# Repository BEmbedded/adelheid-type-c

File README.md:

# Work In Progress
Copied in the USB-C port from the ArisuTea port.

# 𝕬𝖉𝖊𝖑𝖍𝖊𝖎𝖉

The Adelheid is a 75% Alice-like keyboard.  
It's a fork of FateNozomi's Arisu files: [Arisu PCB](https://github.com/FateNozomi/arisu-pcb) &amp; [Arisu case](https://github.com/FateNozomi/arisu-case)

<!--  -->

This repository includes files for:

- the Adelheid PCB &rarr; [README.md](./pcb/README.md)
- a layered case &rarr; [README.md](./case/README.md)
- a wrist rest &rarr; [README.md](./wrist-rest/README.md)

## Changes in this fork

Here is a list of things I added in this fork in comparison to the Arisu:

- [x] added an angled &amp; spaced function row
- [x] added option for stepped caps lock
- [x] replaced micro usb port with tht mini usb port
- [x] added single color underglow and key lighting

for a visual comparison see [here](./IMAGES.md#arisu-comparison)

## Layout

A spaced 75% layout on top of the Alice/Arisu-layout.

[Keyboard-Layout-Editor](http://www.keyboard-layout-editor.com/#/gists/4262535adb5ac81a913edbebc4de8226) [(raw)](https://gist.github.com/floookay/4262535adb5ac81a913edbebc4de8226)  
  
<!--  -->

## Firmware

In the QMK repository: <https://github.com/qmk/qmk_firmware/tree/master/keyboards/adelheid>  
And the online configurator: https://config.qmk.fm/#/adelheid/LAYOUT

## Images

For more images see [images.md](./IMAGES.md).

## Miscellaneous

> Why?

I think accessing the function keys with a layer on the number row is the superior method as it's faster and more comfortable because you barely have to move your hands. I found myself trying to access the function row one-handedly quite often and nothing beats the comfort of pressing a single dedicated key. By default you can still access the function keys via the number row on the secondary layer.

> Where does the name Adelheid come from?

I thought it'd be nice to continue the somewhat tradition of naming Alice-clones by putting a spin on the forename Alice, just like the Arisu, Lisa and Majbritt did. I chose Adelheid as a German spin on the name.  
The typeface is called Fraktur and was the dominant typeface during the time when Adelheid was one of the most popular names.

> Will you add more keys to the bottom row or a second B key?

I don't plan on changing the bottom row or adding a second B key. In my opinion the keyboard looks the best and most balanced the way Fate designed it.

## TODO's

- add 3d printable case files

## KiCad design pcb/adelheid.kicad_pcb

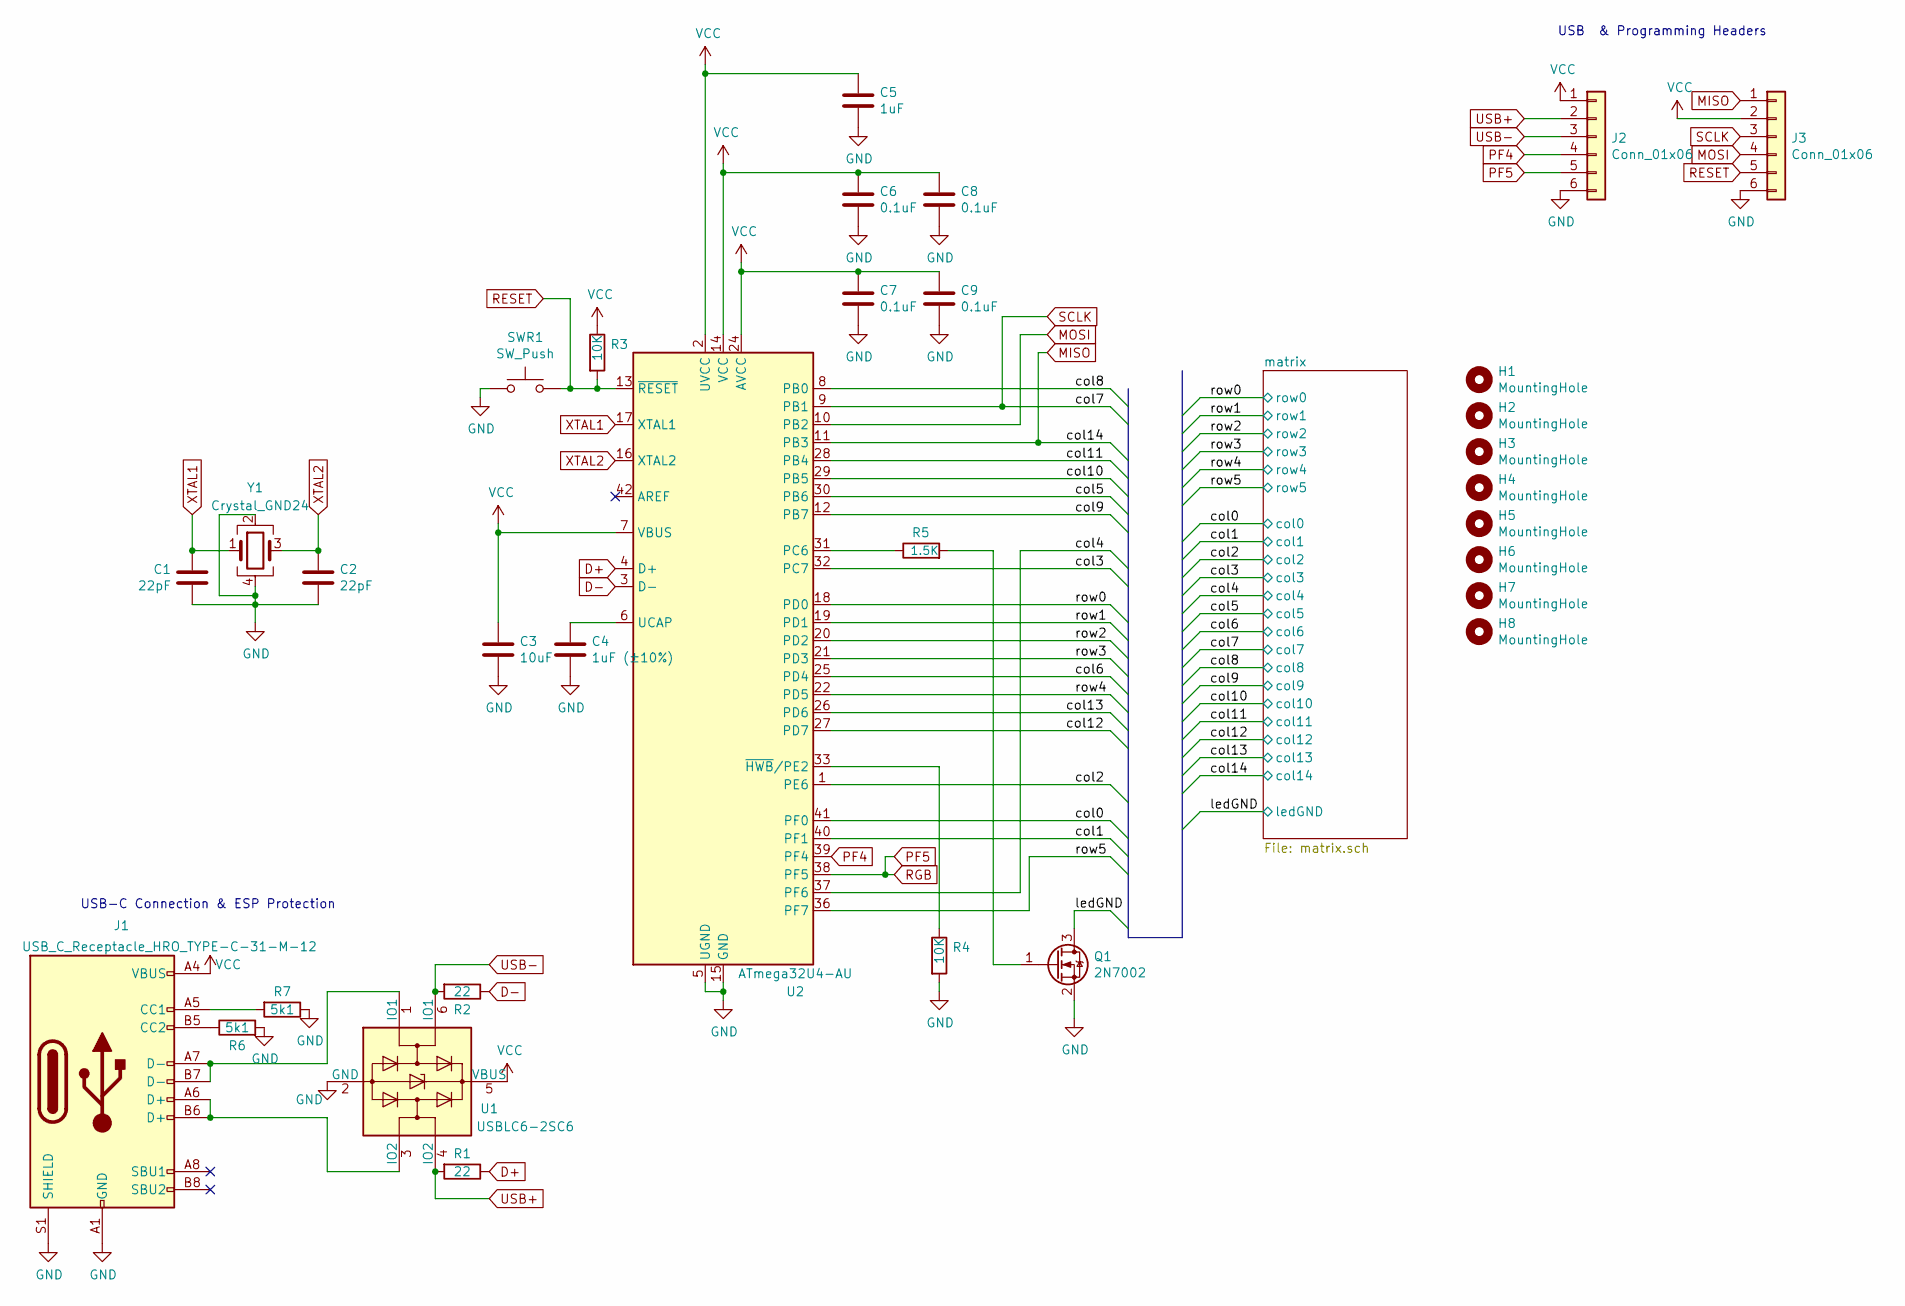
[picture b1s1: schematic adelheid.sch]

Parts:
C1, C2: 22pF; C_0805_HandSoldering; LCSC C1804
C3: 10uF; C_0805_HandSoldering; LCSC C15850
C4: 1uF (±10%); C_0805_HandSoldering; LCSC C28323
C5: 1uF; C_0805_HandSoldering; LCSC C28323
C6, C7, C8, C9: 0.1uF; C_0805_HandSoldering; LCSC C49678
H1, H2, H3, H4, H5, H6, H7, H8: MountingHole; MountingHole_2.2mm_M2_Pad
J1: USB_C_Receptacle_HRO_TYPE-C-31-M-12; USB_C_Receptacle_HRO_TYPE-C-31-M-12-HandSoldering; LCSC C319148
J2, J3: Conn_01x06; PinHeader_1x06_P2.54mm_Vertical
Q1: 2N7002; SOT-23; LCSC C8545
R1, R2: 22; R_0805_2012Metric_Pad1.15x1.40mm_HandSolder; LCSC C17561
R3, R4: 10K; R_0805_2012Metric_Pad1.15x1.40mm_HandSolder; LCSC C17414
R5: 1.5K; R_0805_2012Metric_Pad1.15x1.40mm_HandSolder; LCSC C4310
R6, R7: 5k1; R_0805_2012Metric_Pad1.20x1.40mm_HandSolder; LCSC C27834
SWR1: SW_Push; SW_SPST_TL3342; LCSC C318884
U1: USBLC6-2SC6; SOT-23-6_Handsoldering; LCSC C7519
U2: ATmega32U4-AU; TQFP-44_10x10mm_Pitch0.8mm; LCSC C44854
Y1: Crystal_GND24; Crystal_SMD_SeikoEpson_FA238-4pin_3.2x2.5mm_HandSoldering; LCSC C13738

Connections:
/col0: U2.41 (PF0); also elsewhere on the board
/col1: U2.40 (PF1); also elsewhere on the board
/col2: U2.1 (PE6); also elsewhere on the board
/col3: U2.32 (PC7); also elsewhere on the board
/col4: U2.37 (PF6); also elsewhere on the board
/col5: U2.30 (PB6); also elsewhere on the board
/col6: U2.25 (PD4); also elsewhere on the board
/col8: U2.8 (PB0); also elsewhere on the board
/col9: U2.12 (PB7); also elsewhere on the board
/col10: U2.29 (PB5); also elsewhere on the board
/col11: U2.28 (PB4); also elsewhere on the board
/col12: U2.27 (PD7); also elsewhere on the board
/col13: U2.26 (PD6); also elsewhere on the board
/ledGND: Q1.3 (D); also elsewhere on the board
/row0: U2.18 (PD0); also elsewhere on the board
/row1: U2.19 (PD1); also elsewhere on the board
/row2: U2.20 (PD2); also elsewhere on the board
/row3: U2.21 (PD3); also elsewhere on the board
/row4: U2.22 (PD5); also elsewhere on the board
/row5: U2.36 (PF7); also elsewhere on the board
D+: R1.1, U2.4 (D+)
D-: R2.1, U2.3 (D-)
GND: C1.1, C2.2, C3.2, C4.2, C5.2, C6.2, C7.2, C8.2, C9.2, J1.A1 (GND), J1.A12 (GND), J1.S1 (SHIELD), J2.6, J3.6, Q1.2 (S), R4.2, R6.2, R7.1, SWR1.1, U1.2 (GND), U2.5 (UGND), U2.15 (GND), U2.23 (GND), U2.35 (GND), U2.43 (GND), Y1.2, Y1.4; also elsewhere on the board
MISO: J3.1, U2.11 (PB3); also elsewhere on the board
MOSI: J3.4, U2.10 (PB2)
unnamed: C4.1, U2.6 (UCAP)
unnamed: J1.A5 (CC1), R7.2
unnamed: J1.A6 (D+), J1.B6 (D+), U1.3 (IO2)
unnamed: J1.A7 (D-), J1.B7 (D-), U1.1 (IO1)
unnamed: J1.B5 (CC2), R6.1
unnamed: Q1.1 (G), R5.2
unnamed: R4.1, U2.33 (~HWB~/PE2)
unnamed: R5.1, U2.31 (PC6)
PF4: J2.4, U2.39 (PF4)
PF5: J2.5, U2.38 (PF5); also elsewhere on the board
RESET: J3.5, R3.2, SWR1.2, U2.13 (~RESET)
SCLK: J3.3, U2.9 (PB1); also elsewhere on the board
USB+: J2.2, R1.2, U1.4 (IO2)
USB-: J2.3, R2.2, U1.6 (IO1)
VCC: C3.1, C5.1, C6.1, C7.1, C8.1, C9.1, J1.A4 (VBUS), J1.A9 (VBUS), J2.1, J3.2, R3.1, U1.5 (VBUS), U2.2 (UVCC), U2.7 (VBUS), U2.14 (VCC), U2.24 (AVCC), U2.34 (VCC), U2.44 (AVCC); also elsewhere on the board
XTAL1: C1.2, U2.17 (XTAL1), Y1.1
XTAL2: C2.1, U2.16 (XTAL2), Y1.3

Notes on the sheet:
USB & Programming Headers
USB-C Connection & ESP Protection

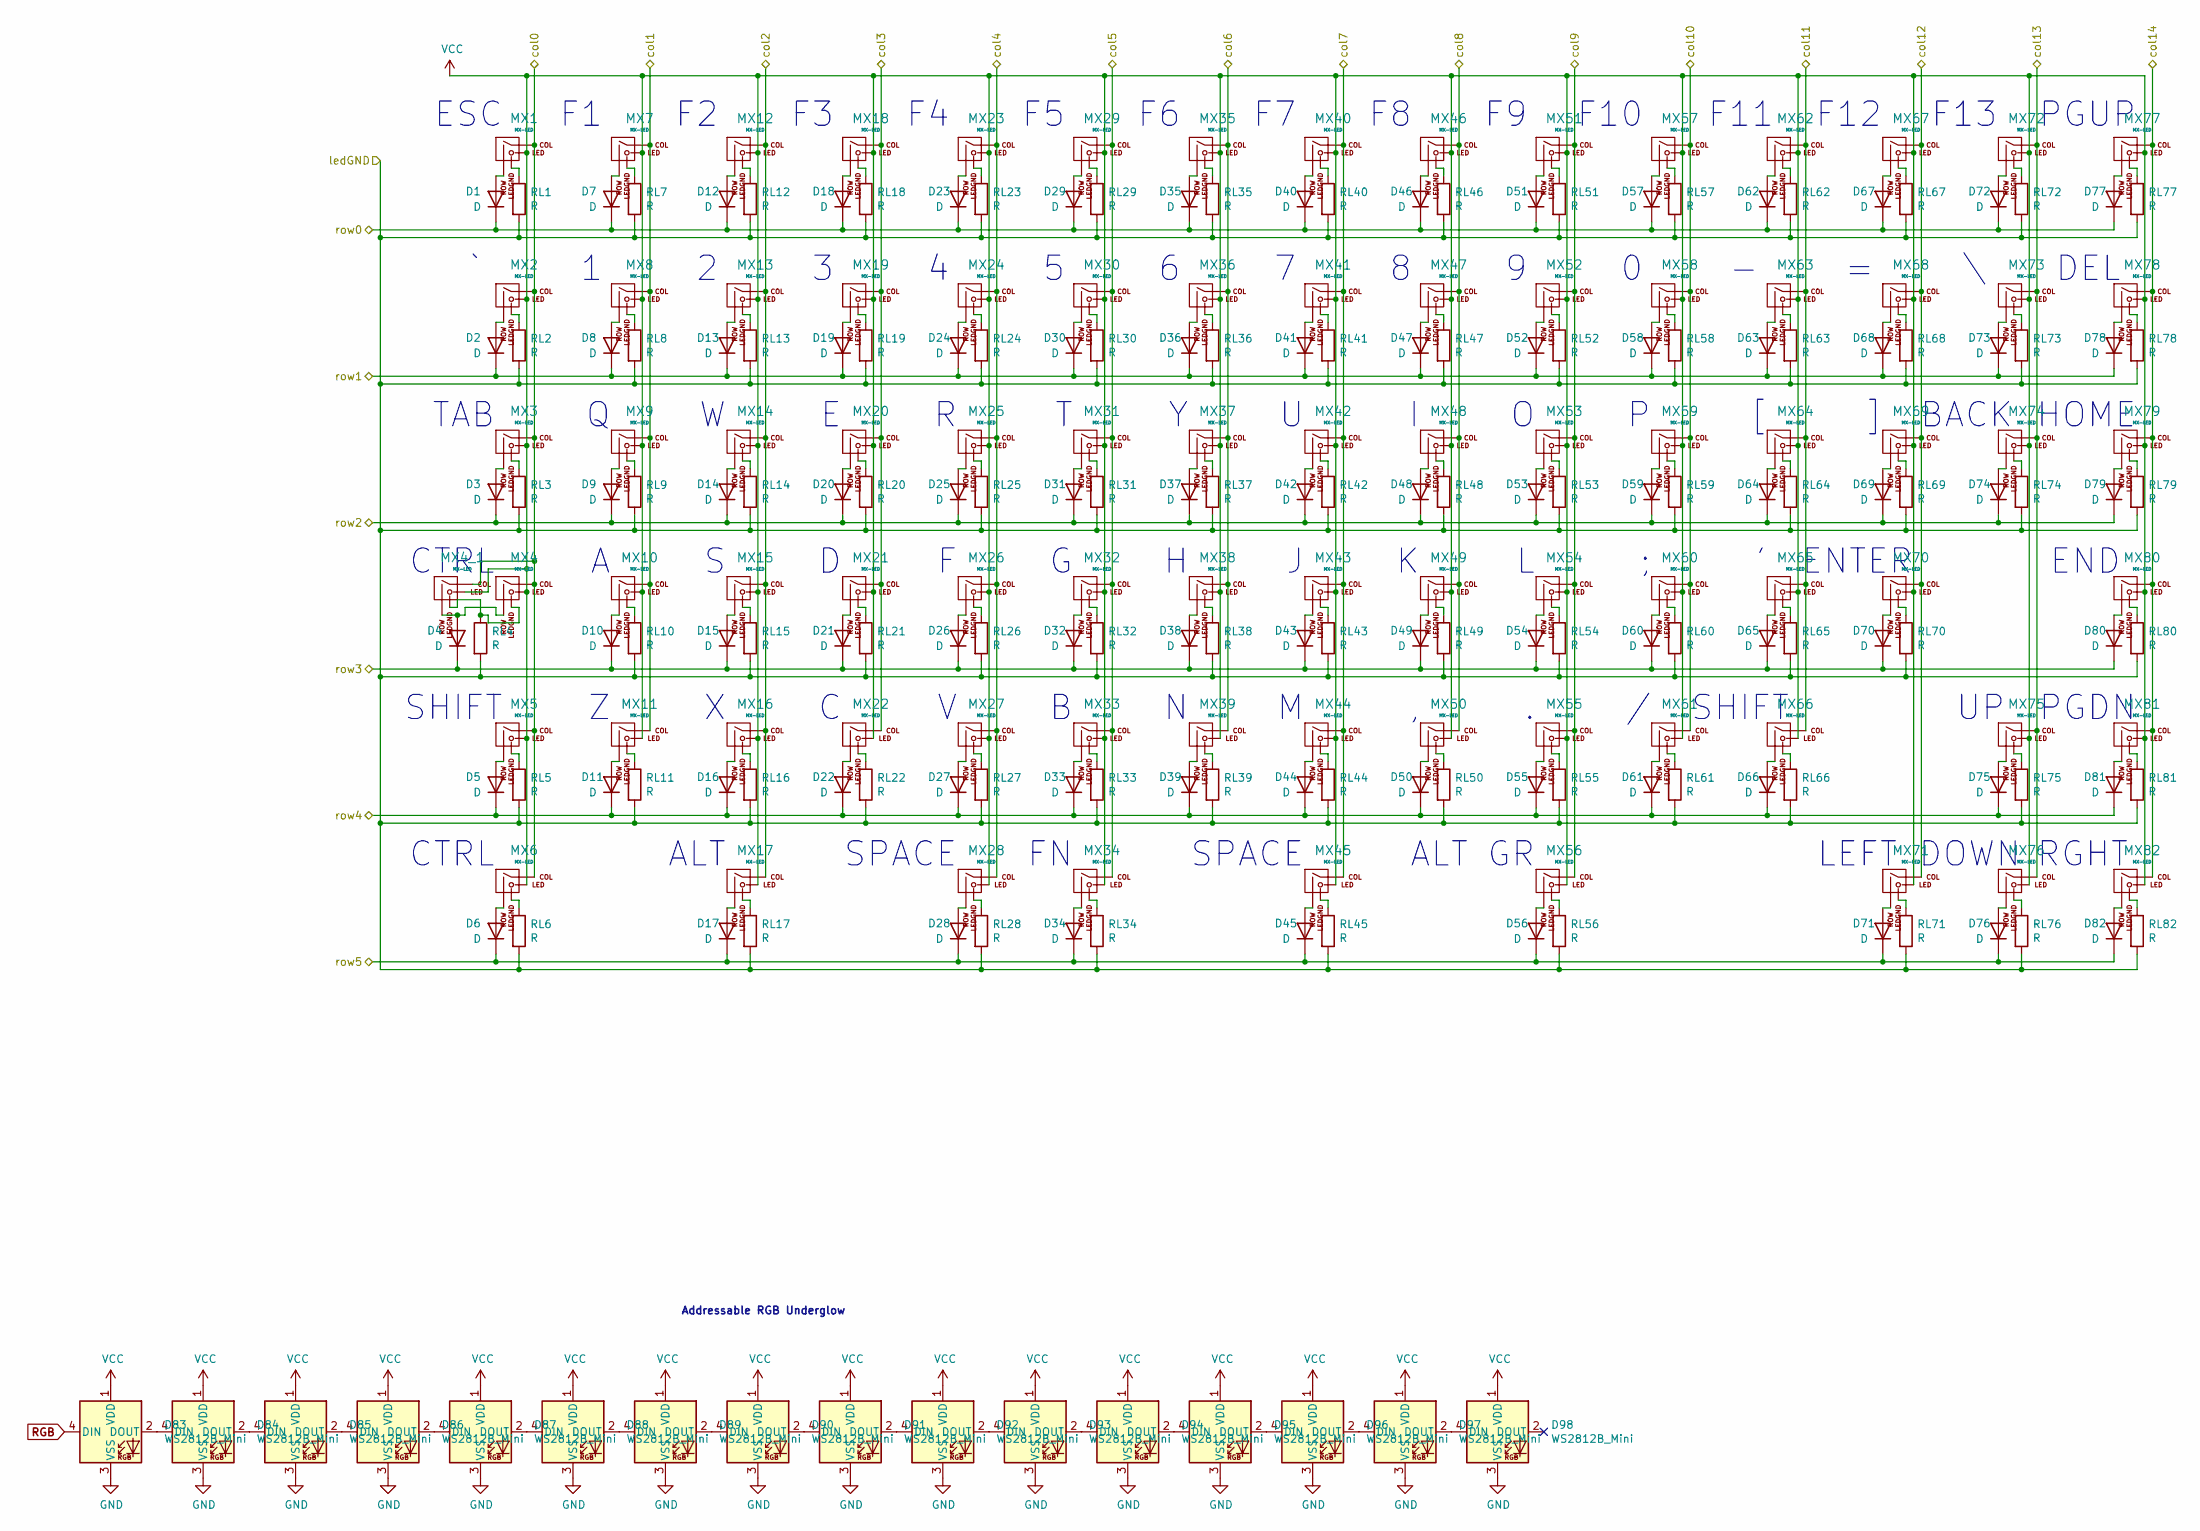
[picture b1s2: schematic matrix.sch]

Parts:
D1, D2, D3, D4, D5, D6, D7, D8, D9, D10, D11, D12, D13, D14, D15, D16, D17, D18, D19, D20, D21, D22, D23, D24, D25, D26, D27, D28, D29, D30, D31, D32, D33, D34, D35, D36, D37, D38, D39, D40, D41, D42, D43, D44, D45, D46, D47, D48, D49, D50, D51, D52, D53, D54, D55, D56, D57, D58, D59, D60, D61, D62, D63, D64, D65, D66, D67, D68, D69, D70, D71, D72, D73, D74, D75, D76, D77, D78, D79, D80, D81, D82: D; D_SOD-123; LCSC C241939
D83, D84, D85, D86, D87, D88, D89, D90, D91, D92, D93, D94, D95, D96, D97, D98: WS2812B_Mini; LED_SK6812MINI_PLCC4_3.5x3.5mm_P1.75mm; LCSC C114583
MX1, MX2, MX7, MX8, MX9, MX10, MX11, MX12, MX13, MX14, MX15, MX16, MX18, MX19, MX20, MX21, MX22, MX23, MX24, MX25, MX26, MX27, MX29, MX30, MX31, MX32, MX33, MX34, MX35, MX36, MX37, MX38, MX39, MX40, MX41, MX42, MX43, MX44, MX46, MX47, MX48, MX49, MX50, MX51, MX52, MX53, MX54, MX55, MX57, MX58, MX59, MX60, MX61, MX62, MX63, MX64, MX65, MX67, MX68, MX69, MX71, MX72, MX73, MX75, MX76, MX77, MX78, MX79, MX80, MX81, MX82: MX-LED; MXOnly-1U
MX3, MX6, MX17, MX56, MX74: MX-LED; MXOnly-1.5U
MX4, MX66: MX-LED; MXOnly-1.75U
MX4_1: MX-LED; MXOnly-1.75U-FLIPPED
MX5: MX-LED; MXOnly-2.25U
MX28: MX-LED; MXOnly-2U-ReversedStabilizers
MX45: MX-LED; MXOnly-2.75U-ReversedStabilizers
MX70: MX-LED; MXOnly-2.25U-ReversedStabilizers
RL1, RL2, RL3, RL4, RL5, RL6, RL7, RL8, RL9, RL10, RL11, RL12, RL13, RL14, RL15, RL16, RL17, RL18, RL19, RL20, RL21, RL22, RL23, RL24, RL25, RL26, RL27, RL28, RL29, RL30, RL31, RL32, RL33, RL34, RL35, RL36, RL37, RL38, RL39, RL40, RL41, RL42, RL43, RL44, RL45, RL46, RL47, RL48, RL49, RL50, RL51, RL52, RL53, RL54, RL55, RL56, RL57, RL58, RL59, RL60, RL61, RL62, RL63, RL64, RL65, RL66, RL67, RL68, RL69, RL70, RL71, RL72, RL73, RL74, RL75, RL76, RL77, RL78, RL79, RL80, RL81, RL82: R; R_0805_2012Metric_Pad1.15x1.40mm_HandSolder; LCSC C17798-DNP

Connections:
/col0: MX1.1 (COL), MX2.1 (COL), MX3.1 (COL), MX4.1 (COL), MX4_1.1 (COL), MX5.1 (COL), MX6.1 (COL); also elsewhere on the board
/col1: MX7.1 (COL), MX8.1 (COL), MX9.1 (COL), MX10.1 (COL), MX11.1 (COL); also elsewhere on the board
/col2: MX12.1 (COL), MX13.1 (COL), MX14.1 (COL), MX15.1 (COL), MX16.1 (COL), MX17.1 (COL); also elsewhere on the board
/col3: MX18.1 (COL), MX19.1 (COL), MX20.1 (COL), MX21.1 (COL), MX22.1 (COL); also elsewhere on the board
/col4: MX23.1 (COL), MX24.1 (COL), MX25.1 (COL), MX26.1 (COL), MX27.1 (COL), MX28.1 (COL); also elsewhere on the board
/col5: MX29.1 (COL), MX30.1 (COL), MX31.1 (COL), MX32.1 (COL), MX33.1 (COL), MX34.1 (COL); also elsewhere on the board
/col6: MX35.1 (COL), MX36.1 (COL), MX37.1 (COL), MX38.1 (COL), MX39.1 (COL); also elsewhere on the board
/col8: MX46.1 (COL), MX47.1 (COL), MX48.1 (COL), MX49.1 (COL), MX50.1 (COL); also elsewhere on the board
/col9: MX51.1 (COL), MX52.1 (COL), MX53.1 (COL), MX54.1 (COL), MX55.1 (COL), MX56.1 (COL); also elsewhere on the board
/col10: MX57.1 (COL), MX58.1 (COL), MX59.1 (COL), MX60.1 (COL), MX61.1 (COL); also elsewhere on the board
/col11: MX62.1 (COL), MX63.1 (COL), MX64.1 (COL), MX65.1 (COL), MX66.1 (COL); also elsewhere on the board
/col12: MX67.1 (COL), MX68.1 (COL), MX69.1 (COL), MX70.1 (COL), MX71.1 (COL); also elsewhere on the board
/col13: MX72.1 (COL), MX73.1 (COL), MX74.1 (COL), MX75.1 (COL), MX76.1 (COL); also elsewhere on the board
/ledGND: RL1.2, RL2.2, RL3.2, RL4.2, RL5.2, RL6.2, RL7.2, RL8.2, RL9.2, RL10.2, RL11.2, RL12.2, RL13.2, RL14.2, RL15.2, RL16.2, RL17.2, RL18.2, RL19.2, RL20.2, RL21.2, RL22.2, RL23.2, RL24.2, RL25.2, RL26.2, RL27.2, RL28.2, RL29.2, RL30.2, RL31.2, RL32.2, RL33.2, RL34.2, RL35.2, RL36.2, RL37.2, RL38.2, RL39.2, RL40.2, RL41.2, RL42.2, RL43.2, RL44.2, RL45.2, RL46.2, RL47.2, RL48.2, RL49.2, RL50.2, RL51.2, RL52.2, RL53.2, RL54.2, RL55.2, RL56.2, RL57.2, RL58.2, RL59.2, RL60.2, RL61.2, RL62.2, RL63.2, RL64.2, RL65.2, RL66.2, RL67.2, RL68.2, RL69.2, RL70.2, RL71.2, RL72.2, RL73.2, RL74.2, RL75.2, RL76.2, RL77.2, RL78.2, RL79.2, RL80.2, RL81.2, RL82.2; also elsewhere on the board
/row0: D1.1 (K), D7.1 (K), D12.1 (K), D18.1 (K), D23.1 (K), D29.1 (K), D35.1 (K), D40.1 (K), D46.1 (K), D51.1 (K), D57.1 (K), D62.1 (K), D67.1 (K), D72.1 (K), D77.1 (K); also elsewhere on the board
/row1: D2.1 (K), D8.1 (K), D13.1 (K), D19.1 (K), D24.1 (K), D30.1 (K), D36.1 (K), D41.1 (K), D47.1 (K), D52.1 (K), D58.1 (K), D63.1 (K), D68.1 (K), D73.1 (K), D78.1 (K); also elsewhere on the board
/row2: D3.1 (K), D9.1 (K), D14.1 (K), D20.1 (K), D25.1 (K), D31.1 (K), D37.1 (K), D42.1 (K), D48.1 (K), D53.1 (K), D59.1 (K), D64.1 (K), D69.1 (K), D74.1 (K), D79.1 (K); also elsewhere on the board
/row3: D4.1 (K), D10.1 (K), D15.1 (K), D21.1 (K), D26.1 (K), D32.1 (K), D38.1 (K), D43.1 (K), D49.1 (K), D54.1 (K), D60.1 (K), D65.1 (K), D70.1 (K), D80.1 (K); also elsewhere on the board
/row4: D5.1 (K), D11.1 (K), D16.1 (K), D22.1 (K), D27.1 (K), D33.1 (K), D39.1 (K), D44.1 (K), D50.1 (K), D55.1 (K), D61.1 (K), D66.1 (K), D75.1 (K), D81.1 (K); also elsewhere on the board
/row5: D6.1 (K), D17.1 (K), D28.1 (K), D34.1 (K), D45.1 (K), D56.1 (K), D71.1 (K), D76.1 (K), D82.1 (K); also elsewhere on the board
GND: D83.3 (VSS), D84.3 (VSS), D85.3 (VSS), D86.3 (VSS), D87.3 (VSS), D88.3 (VSS), D89.3 (VSS), D90.3 (VSS), D91.3 (VSS), D92.3 (VSS), D93.3 (VSS), D94.3 (VSS), D95.3 (VSS), D96.3 (VSS), D97.3 (VSS), D98.3 (VSS); also elsewhere on the board
MISO: MX77.1 (COL), MX78.1 (COL), MX79.1 (COL), MX80.1 (COL), MX81.1 (COL), MX82.1 (COL); also elsewhere on the board
unnamed: D1.2 (A), MX1.2 (ROW)
unnamed: D2.2 (A), MX2.2 (ROW)
unnamed: D3.2 (A), MX3.2 (ROW)
unnamed: D4.2 (A), MX4.2 (ROW), MX4_1.2 (ROW)
unnamed: D5.2 (A), MX5.2 (ROW)
unnamed: D6.2 (A), MX6.2 (ROW)
unnamed: D7.2 (A), MX7.2 (ROW)
unnamed: D8.2 (A), MX8.2 (ROW)
unnamed: D9.2 (A), MX9.2 (ROW)
unnamed: D10.2 (A), MX10.2 (ROW)
unnamed: D11.2 (A), MX11.2 (ROW)
unnamed: D12.2 (A), MX12.2 (ROW)
unnamed: D13.2 (A), MX13.2 (ROW)
unnamed: D14.2 (A), MX14.2 (ROW)
unnamed: D15.2 (A), MX15.2 (ROW)
unnamed: D16.2 (A), MX16.2 (ROW)
unnamed: D17.2 (A), MX17.2 (ROW)
unnamed: D18.2 (A), MX18.2 (ROW)
unnamed: D19.2 (A), MX19.2 (ROW)
unnamed: D20.2 (A), MX20.2 (ROW)
unnamed: D21.2 (A), MX21.2 (ROW)
unnamed: D22.2 (A), MX22.2 (ROW)
unnamed: D23.2 (A), MX23.2 (ROW)
unnamed: D24.2 (A), MX24.2 (ROW)
unnamed: D25.2 (A), MX25.2 (ROW)
unnamed: D26.2 (A), MX26.2 (ROW)
unnamed: D27.2 (A), MX27.2 (ROW)
unnamed: D28.2 (A), MX28.2 (ROW)
unnamed: D29.2 (A), MX29.2 (ROW)
unnamed: D30.2 (A), MX30.2 (ROW)
unnamed: D31.2 (A), MX31.2 (ROW)
unnamed: D32.2 (A), MX32.2 (ROW)
unnamed: D33.2 (A), MX33.2 (ROW)
unnamed: D34.2 (A), MX34.2 (ROW)
unnamed: D35.2 (A), MX35.2 (ROW)
unnamed: D36.2 (A), MX36.2 (ROW)
unnamed: D37.2 (A), MX37.2 (ROW)
unnamed: D38.2 (A), MX38.2 (ROW)
unnamed: D39.2 (A), MX39.2 (ROW)
unnamed: D40.2 (A), MX40.2 (ROW)
unnamed: D41.2 (A), MX41.2 (ROW)
unnamed: D42.2 (A), MX42.2 (ROW)
unnamed: D43.2 (A), MX43.2 (ROW)
unnamed: D44.2 (A), MX44.2 (ROW)
unnamed: D45.2 (A), MX45.2 (ROW)
unnamed: D46.2 (A), MX46.2 (ROW)
unnamed: D47.2 (A), MX47.2 (ROW)
unnamed: D48.2 (A), MX48.2 (ROW)
unnamed: D49.2 (A), MX49.2 (ROW)
unnamed: D50.2 (A), MX50.2 (ROW)
unnamed: D51.2 (A), MX51.2 (ROW)
unnamed: D52.2 (A), MX52.2 (ROW)
unnamed: D53.2 (A), MX53.2 (ROW)
unnamed: D54.2 (A), MX54.2 (ROW)
unnamed: D55.2 (A), MX55.2 (ROW)
unnamed: D56.2 (A), MX56.2 (ROW)
unnamed: D57.2 (A), MX57.2 (ROW)
unnamed: D58.2 (A), MX58.2 (ROW)
unnamed: D59.2 (A), MX59.2 (ROW)
unnamed: D60.2 (A), MX60.2 (ROW)
unnamed: D61.2 (A), MX61.2 (ROW)
unnamed: D62.2 (A), MX62.2 (ROW)
unnamed: D63.2 (A), MX63.2 (ROW)
unnamed: D64.2 (A), MX64.2 (ROW)
unnamed: D65.2 (A), MX65.2 (ROW)
unnamed: D66.2 (A), MX66.2 (ROW)
unnamed: D67.2 (A), MX67.2 (ROW)
unnamed: D68.2 (A), MX68.2 (ROW)
unnamed: D69.2 (A), MX69.2 (ROW)
unnamed: D70.2 (A), MX70.2 (ROW)
unnamed: D71.2 (A), MX71.2 (ROW)
unnamed: D72.2 (A), MX72.2 (ROW)
unnamed: D73.2 (A), MX73.2 (ROW)
unnamed: D74.2 (A), MX74.2 (ROW)
unnamed: D75.2 (A), MX75.2 (ROW)
unnamed: D76.2 (A), MX76.2 (ROW)
unnamed: D77.2 (A), MX77.2 (ROW)
unnamed: D78.2 (A), MX78.2 (ROW)
unnamed: D79.2 (A), MX79.2 (ROW)
unnamed: D80.2 (A), MX80.2 (ROW)
unnamed: D81.2 (A), MX81.2 (ROW)
unnamed: D82.2 (A), MX82.2 (ROW)
unnamed: D83.2 (DOUT), D84.4 (DIN)
unnamed: D84.2 (DOUT), D85.4 (DIN)
unnamed: D85.2 (DOUT), D86.4 (DIN)
unnamed: D86.2 (DOUT), D87.4 (DIN)
unnamed: D87.2 (DOUT), D88.4 (DIN)
unnamed: D88.2 (DOUT), D89.4 (DIN)
unnamed: D89.2 (DOUT), D90.4 (DIN)
unnamed: D90.2 (DOUT), D91.4 (DIN)
unnamed: D91.2 (DOUT), D92.4 (DIN)
unnamed: D92.2 (DOUT), D93.4 (DIN)
unnamed: D93.2 (DOUT), D94.4 (DIN)
unnamed: D94.2 (DOUT), D95.4 (DIN)
unnamed: D95.2 (DOUT), D96.4 (DIN)
unnamed: D96.2 (DOUT), D97.4 (DIN)
unnamed: D97.2 (DOUT), D98.4 (DIN)
unnamed: MX1.4 (LEDGND), RL1.1
unnamed: MX2.4 (LEDGND), RL2.1
unnamed: MX3.4 (LEDGND), RL3.1
unnamed: MX4.4 (LEDGND), MX4_1.4 (LEDGND), RL4.1
unnamed: MX5.4 (LEDGND), RL5.1
unnamed: MX6.4 (LEDGND), RL6.1
unnamed: MX7.4 (LEDGND), RL7.1
unnamed: MX8.4 (LEDGND), RL8.1
unnamed: MX9.4 (LEDGND), RL9.1
unnamed: MX10.4 (LEDGND), RL10.1
unnamed: MX11.4 (LEDGND), RL11.1
unnamed: MX12.4 (LEDGND), RL12.1
unnamed: MX13.4 (LEDGND), RL13.1
unnamed: MX14.4 (LEDGND), RL14.1
unnamed: MX15.4 (LEDGND), RL15.1
unnamed: MX16.4 (LEDGND), RL16.1
unnamed: MX17.4 (LEDGND), RL17.1
unnamed: MX18.4 (LEDGND), RL18.1
unnamed: MX19.4 (LEDGND), RL19.1
unnamed: MX20.4 (LEDGND), RL20.1
unnamed: MX21.4 (LEDGND), RL21.1
unnamed: MX22.4 (LEDGND), RL22.1
unnamed: MX23.4 (LEDGND), RL23.1
unnamed: MX24.4 (LEDGND), RL24.1
unnamed: MX25.4 (LEDGND), RL25.1
unnamed: MX26.4 (LEDGND), RL26.1
unnamed: MX27.4 (LEDGND), RL27.1
unnamed: MX28.4 (LEDGND), RL28.1
unnamed: MX29.4 (LEDGND), RL29.1
unnamed: MX30.4 (LEDGND), RL30.1
unnamed: MX31.4 (LEDGND), RL31.1
unnamed: MX32.4 (LEDGND), RL32.1
unnamed: MX33.4 (LEDGND), RL33.1
unnamed: MX34.4 (LEDGND), RL34.1
unnamed: MX35.4 (LEDGND), RL35.1
unnamed: MX36.4 (LEDGND), RL36.1
unnamed: MX37.4 (LEDGND), RL37.1
unnamed: MX38.4 (LEDGND), RL38.1
unnamed: MX39.4 (LEDGND), RL39.1
unnamed: MX40.4 (LEDGND), RL40.1
unnamed: MX41.4 (LEDGND), RL41.1
unnamed: MX42.4 (LEDGND), RL42.1
unnamed: MX43.4 (LEDGND), RL43.1
unnamed: MX44.4 (LEDGND), RL44.1
unnamed: MX45.4 (LEDGND), RL45.1
unnamed: MX46.4 (LEDGND), RL46.1
unnamed: MX47.4 (LEDGND), RL47.1
unnamed: MX48.4 (LEDGND), RL48.1
unnamed: MX49.4 (LEDGND), RL49.1
unnamed: MX50.4 (LEDGND), RL50.1
unnamed: MX51.4 (LEDGND), RL51.1
unnamed: MX52.4 (LEDGND), RL52.1
unnamed: MX53.4 (LEDGND), RL53.1
unnamed: MX54.4 (LEDGND), RL54.1
unnamed: MX55.4 (LEDGND), RL55.1
unnamed: MX56.4 (LEDGND), RL56.1
unnamed: MX57.4 (LEDGND), RL57.1
unnamed: MX58.4 (LEDGND), RL58.1
unnamed: MX59.4 (LEDGND), RL59.1
unnamed: MX60.4 (LEDGND), RL60.1
unnamed: MX61.4 (LEDGND), RL61.1
unnamed: MX62.4 (LEDGND), RL62.1
unnamed: MX63.4 (LEDGND), RL63.1
unnamed: MX64.4 (LEDGND), RL64.1
unnamed: MX65.4 (LEDGND), RL65.1
unnamed: MX66.4 (LEDGND), RL66.1
unnamed: MX67.4 (LEDGND), RL67.1
unnamed: MX68.4 (LEDGND), RL68.1
unnamed: MX69.4 (LEDGND), RL69.1
unnamed: MX70.4 (LEDGND), RL70.1
unnamed: MX71.4 (LEDGND), RL71.1
unnamed: MX72.4 (LEDGND), RL72.1
unnamed: MX73.4 (LEDGND), RL73.1
unnamed: MX74.4 (LEDGND), RL74.1
unnamed: MX75.4 (LEDGND), RL75.1
unnamed: MX76.4 (LEDGND), RL76.1
unnamed: MX77.4 (LEDGND), RL77.1
unnamed: MX78.4 (LEDGND), RL78.1
unnamed: MX79.4 (LEDGND), RL79.1
unnamed: MX80.4 (LEDGND), RL80.1
unnamed: MX81.4 (LEDGND), RL81.1
unnamed: MX82.4 (LEDGND), RL82.1
PF5: D83.4 (DIN); also elsewhere on the board
SCLK: MX40.1 (COL), MX41.1 (COL), MX42.1 (COL), MX43.1 (COL), MX44.1 (COL), MX45.1 (COL); also elsewhere on the board
VCC: D83.1 (VDD), D84.1 (VDD), D85.1 (VDD), D86.1 (VDD), D87.1 (VDD), D88.1 (VDD), D89.1 (VDD), D90.1 (VDD), D91.1 (VDD), D92.1 (VDD), D93.1 (VDD), D94.1 (VDD), D95.1 (VDD), D96.1 (VDD), D97.1 (VDD), D98.1 (VDD), MX1.3 (LED), MX2.3 (LED), MX3.3 (LED), MX4.3 (LED), MX4_1.3 (LED), MX5.3 (LED), MX6.3 (LED), MX7.3 (LED), MX8.3 (LED), MX9.3 (LED), MX10.3 (LED), MX11.3 (LED), MX12.3 (LED), MX13.3 (LED), MX14.3 (LED), MX15.3 (LED), MX16.3 (LED), MX17.3 (LED), MX18.3 (LED), MX19.3 (LED), MX20.3 (LED), MX21.3 (LED), MX22.3 (LED), MX23.3 (LED), MX24.3 (LED), MX25.3 (LED), MX26.3 (LED), MX27.3 (LED), MX28.3 (LED), MX29.3 (LED), MX30.3 (LED), MX31.3 (LED), MX32.3 (LED), MX33.3 (LED), MX34.3 (LED), MX35.3 (LED), MX36.3 (LED), MX37.3 (LED), MX38.3 (LED), MX39.3 (LED), MX40.3 (LED), MX41.3 (LED), MX42.3 (LED), MX43.3 (LED), MX44.3 (LED), MX45.3 (LED), MX46.3 (LED), MX47.3 (LED), MX48.3 (LED), MX49.3 (LED), MX50.3 (LED), MX51.3 (LED), MX52.3 (LED), MX53.3 (LED), MX54.3 (LED), MX55.3 (LED), MX56.3 (LED), MX57.3 (LED), MX58.3 (LED), MX59.3 (LED), MX60.3 (LED), MX61.3 (LED), MX62.3 (LED), MX63.3 (LED), MX64.3 (LED), MX65.3 (LED), MX66.3 (LED), MX67.3 (LED), MX68.3 (LED), MX69.3 (LED), MX70.3 (LED), MX71.3 (LED), MX72.3 (LED), MX73.3 (LED), MX74.3 (LED), MX75.3 (LED), MX76.3 (LED), MX77.3 (LED), MX78.3 (LED), MX79.3 (LED), MX80.3 (LED), MX81.3 (LED), MX82.3 (LED); also elsewhere on the board

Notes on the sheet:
ESC
F10
F11
F12
F13
PGUP
DEL
HOME
END
PGDN
RGHT
DOWN
LEFT
TAB
BACK
CTRL
ENTER
SHIFT
ALT
SPACE
ALT GR
Addressable RGB Underglow

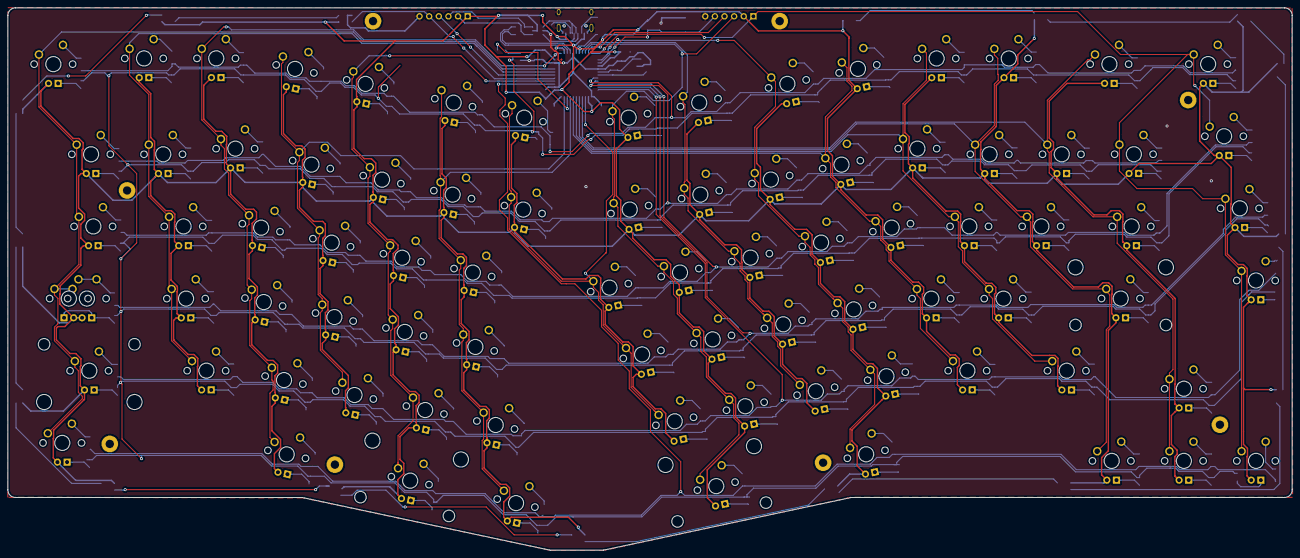
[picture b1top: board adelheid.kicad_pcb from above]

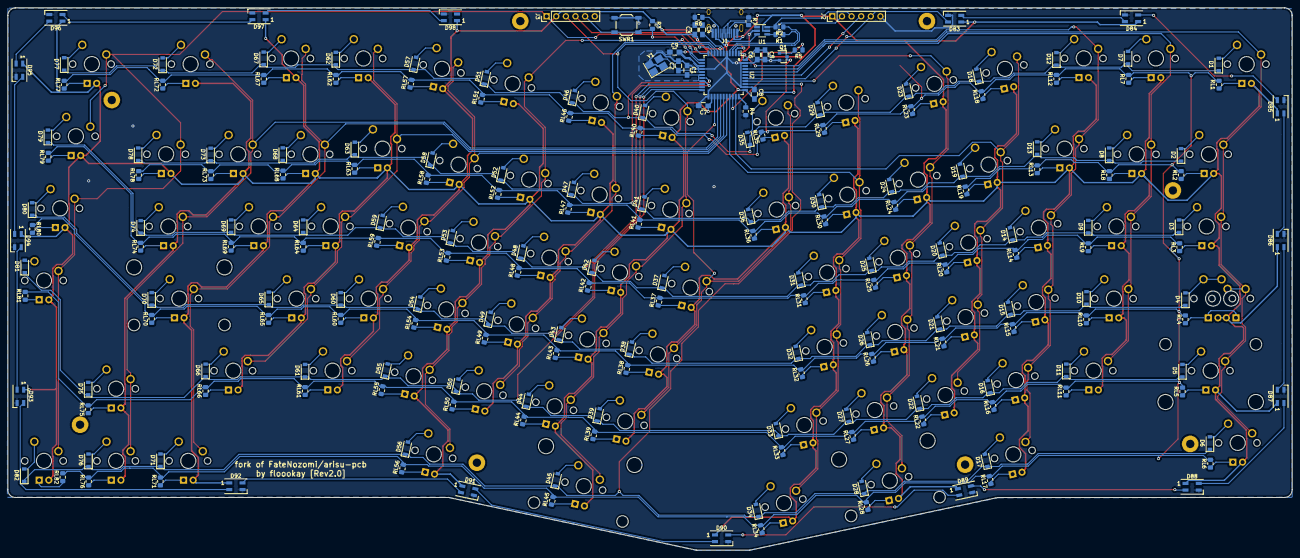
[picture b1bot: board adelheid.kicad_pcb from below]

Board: 2 copper layers, 339.1 x 143.2 mm, 295 parts (204 on the bottom side), 221 nets.

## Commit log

2021-07-30 Copy in arisutea.pretty
2021-07-30 Converted Adelheid mini USB to Aristutea USB-C
2021-07-30 Cleanup a bunch of USB tracks to significantly increase copper fill area
2021-07-31 Cleanup a couple more VCC and GND's for the micro.
2021-07-31 Regenerate Gerber's as per JLCPCB instructions
2021-07-31 Generate pick and place files for JLCPCB
2021-07-31 Copy in the USB connector files from the Arisutea repo
2021-07-31 Updated schematic to replace Mini USB with USB-C and Add ARGB headers
2021-07-31 Replace single colour underglow and RGB headers for WS2812B Addressable SMD LED
2021-07-31 Update all components with JLCPCB part numbers
2021-07-31 Created updated bomb
2021-07-31 Fix missing footprints
2021-07-31 WIP: CLeaning up old tracks and starting to layout new components.
2021-07-31 Fixed missing VCC for USB connector and incorrect DIN/DOUT for underground LED's
2021-08-01 Replaced WS21812B with mini version and connected all track. (post clean up commit)
2021-08-01 Fixed key that had accidentally been deleted! cleaned up any DRC markers.
2021-08-01 Add a couple of via to clean up a couple gaps in the ground plane
2021-08-01 Regenerate all files to for release to JLCPCB
